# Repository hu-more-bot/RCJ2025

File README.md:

# RCJ2025
F1 Car Software & Hardware
> Huge thanks to [the6p4c](https://github.com/the6p4c/rp2040_ov2640) for his camera implementation

> More documentation is coming soon!

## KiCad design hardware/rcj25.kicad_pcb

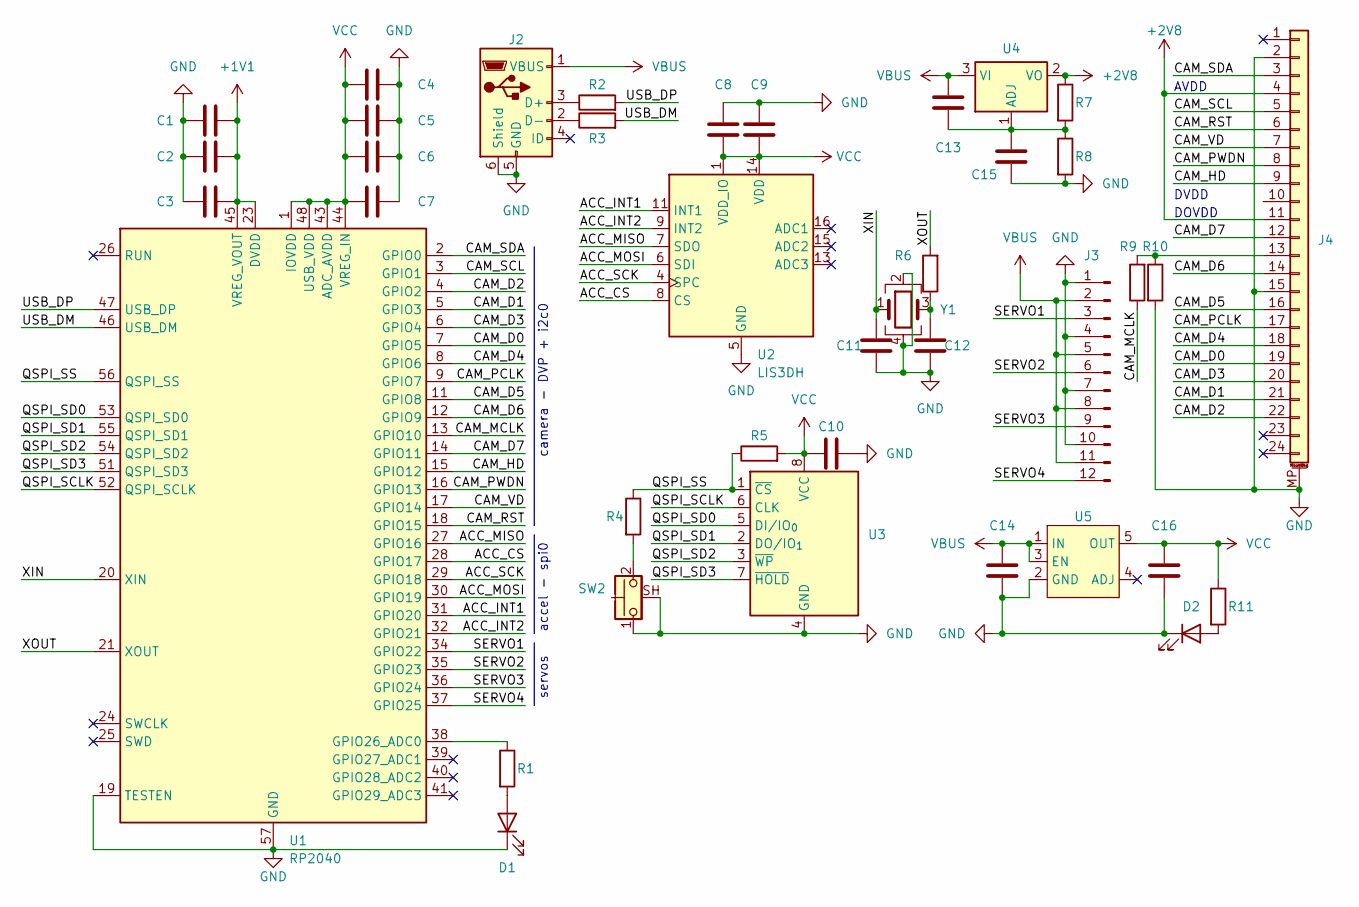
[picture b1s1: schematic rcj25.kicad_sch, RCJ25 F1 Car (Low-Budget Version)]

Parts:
C1, C2, C4, C5, C6, C8, C10: 100n; C_0603_1608Metric
C3, C7, C14, C16: 1u; C_0603_1608Metric
C9: 10u; C_0603_1608Metric
C11, C12, C13, C15: C; C_0603_1608Metric
D1: LED; LED_0603_1608Metric
D2: pwr; LED_0603_1608Metric
J2: USB_B_Micro; SHOUHAN_MicroQTJ
J3: Conn_01x12_Pin; PinHeader_3x04_P2.54mm_Vertical
J4: Conn_01x24_MountingPin; PCA-6G-24-HL-3
R1, R7, R8, R11: R; R_0603_1608Metric
R2, R3: 27.4; R_0603_1608Metric
R4, R6: 1k; R_0603_1608Metric
R5: DNF; R_0603_1608Metric
R9, R10: 4.7k; R_0603_1608Metric
SW2: SW_Push_Shielded; KSM632B
U1: RP2040; QFN-56-1EP_7x7mm_P0.4mm_EP3.2x3.2mm
U2: LIS3DH; LGA-16_3x3mm_P0.5mm_LayoutBorder3x5y
U3: W25X40CLSV; SOIC-8_5.3x5.3mm_P1.27mm
U4: LM1117MP-ADJ; SOT-223-3_TabPin2
U5: AP7365; SOT-23-5
Y1: Crystal_GND24; Crystal_SMD_3225-4Pin_3.2x2.5mm

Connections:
+1V1: C1.2, C2.2, C3.2, U1.23 (DVDD), U1.45 (VREG_VOUT), U1.50 (DVDD)
+2V8: J4.4, J4.11, R7.1, U4.2 (VO)
/ACC_CS: U1.28 (GPIO17), U2.8 (CS)
/ACC_INT1: U1.31 (GPIO20), U2.11 (INT1)
/ACC_INT2: U1.32 (GPIO21), U2.9 (INT2)
/ACC_MISO: U1.27 (GPIO16), U2.7 (SDO)
/ACC_MOSI: U1.30 (GPIO19), U2.6 (SDI)
/ACC_SCK: U1.29 (GPIO18), U2.4 (SPC)
/CAM_D0: J4.19, U1.7 (GPIO5)
/CAM_D1: J4.21, U1.5 (GPIO3)
/CAM_D2: J4.22, U1.4 (GPIO2)
/CAM_D3: J4.20, U1.6 (GPIO4)
/CAM_D4: J4.18, U1.8 (GPIO6)
/CAM_D5: J4.16, U1.11 (GPIO8)
/CAM_D6: J4.14, U1.12 (GPIO9)
/CAM_D7: J4.12, U1.14 (GPIO11)
/CAM_HD: J4.9, U1.15 (GPIO12)
/CAM_MCLK: R9.1, U1.13 (GPIO10)
/CAM_PCLK: J4.17, U1.9 (GPIO7)
/CAM_PWDN: J4.8, U1.16 (GPIO13)
/CAM_RST: J4.6, U1.18 (GPIO15)
/CAM_SCL: J4.5, U1.3 (GPIO1)
/CAM_SDA: J4.3, U1.2 (GPIO0)
/CAM_VD: J4.7, U1.17 (GPIO14)
/QSPI_SCLK: U1.52 (QSPI_SCLK), U3.6 (CLK)
/QSPI_SD0: U1.53 (QSPI_SD0), U3.5 (DI/IO_{0})
/QSPI_SD1: U1.55 (QSPI_SD1), U3.2 (DO/IO_{1})
/QSPI_SD2: U1.54 (QSPI_SD2), U3.3 (~WP)
/QSPI_SD3: U1.51 (QSPI_SD3), U3.7 (~HOLD)
/QSPI_SS: R4.1, R5.1, U1.56 (QSPI_SS), U3.1 (~CS)
/SERVO1: J3.3, U1.34 (GPIO22)
/SERVO2: J3.6, U1.35 (GPIO23)
/SERVO3: J3.9, U1.36 (GPIO24)
/SERVO4: J3.12, U1.37 (GPIO25)
/USB_DM: R3.2, U1.46 (USB_DM)
/USB_DP: R2.2, U1.47 (USB_DP)
/XIN: C11.2, U1.20 (XIN), Y1.1
/XOUT: R6.2, U1.21 (XOUT)
GND: C1.1, C2.1, C3.1, C4.2, C5.2, C6.2, C7.2, C8.1, C9.1, C10.2, C11.1, C12.1, C14.2, C15.2, C16.2, D1.1 (K), D2.1 (K), J2.5 (GND), J2.6 (Shield), J3.1, J3.4, J3.7, J3.10, J4.2, J4.15, J4.MP (MountPin), R8.2, R10.2, SW2.1, SW2.SH (B), U1.19 (TESTEN), U1.57 (GND), U2.5 (GND), U2.10 (GND), U2.12 (GND), U3.4 (GND), U5.2 (GND), Y1.2, Y1.4
unnamed: C12.2, R6.1, Y1.3
unnamed: D1.2 (A), R1.2
unnamed: D2.2 (A), R11.2
unnamed: J2.3 (D+), R2.1
unnamed: J2.2 (D-), R3.1
unnamed: J4.13, R9.2, R10.1
unnamed: R4.2, SW2.2
unnamed: R1.1, U1.38 (GPIO26_ADC0)
unnamed: C13.2, C15.1, R7.2, R8.1, U4.1 (ADJ)
VBUS: C13.1, C14.1, J2.1 (VBUS), J3.2, J3.5, J3.8, J3.11, U4.3 (VI), U5.1 (IN), U5.3 (EN)
VCC: C4.1, C5.1, C6.1, C7.1, C8.2, C9.2, C10.1, C16.1, R5.2, R11.1, U1.1 (IOVDD), U1.10 (IOVDD), U1.22 (IOVDD), U1.33 (IOVDD), U1.42 (IOVDD), U1.43 (ADC_AVDD), U1.44 (VREG_IN), U1.48 (USB_VDD), U1.49 (IOVDD), U2.1 (VDD_IO), U2.14 (VDD), U3.8 (VCC), U5.5 (OUT)

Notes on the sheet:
AVDD
DOVDD
servos
DVDD
accel - spi0
camera - DVP + i2c0

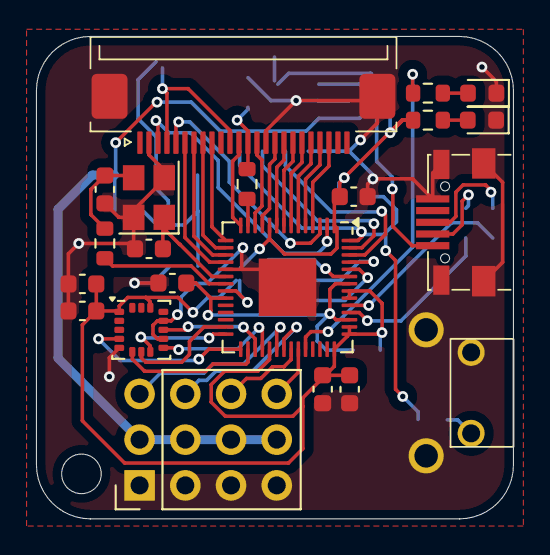
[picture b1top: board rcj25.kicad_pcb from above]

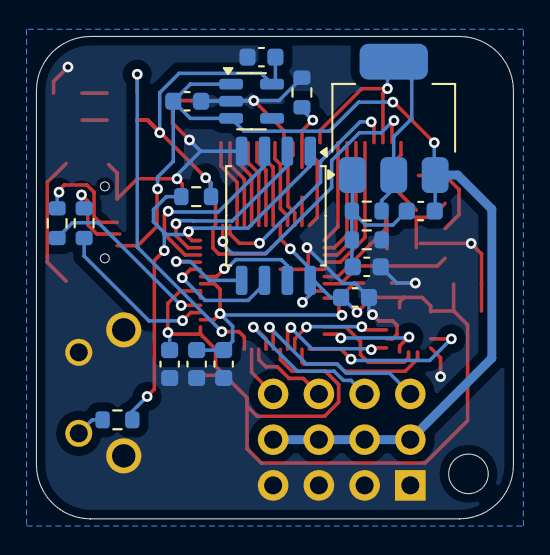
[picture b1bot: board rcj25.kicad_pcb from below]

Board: 2 copper layers, 26.5 x 26.8 mm, 39 parts (18 on the bottom side), 50 nets.

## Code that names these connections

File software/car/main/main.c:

// // #include <boards/pico.h>
#include <hardware/gpio.h>
// #include <hardware/spi.h>
// #include <hardware/i2c.h>
#include <pico/time.h>

#include <motor.h>
// #include <pico/stdio.h>

#define SERVO1 22
#define SERVO2 23
#define SERVO3 24
#define SERVO4 25

int main() {
  // Servo
  motor_init(SERVO2);
  motor_set(SERVO2, 1500);
  
  // BLDC
  sleep_ms(2000);
  motor_init(SERVO1);
  motor_set(SERVO1, 2000);
  sleep_ms(2000);
  motor_set(SERVO1, 1000);
  sleep_ms(2000);
  motor_set(SERVO1, 500);
  sleep_ms(2000);

  // motor_set(SERVO2, 1000);
  // motor_set(SERVO1, 1200);
  // sleep_ms(500);

  // for (int i = 0; i < 16 * 2; i++) {
  //   motor_set(SERVO1, 1100);
  //   sleep_ms(1500);
  //   // motor_set(SERVO1, 1000);
  //   // sleep_ms(300);
  // }

  motor_set(SERVO1, 1200);
  sleep_ms(250);
  motor_set(SERVO1, 1300);
  motor_set(SERVO2, 1000);
  sleep_ms(15000);

  motor_set(SERVO1, 1000);
  
  // motor_set(SERVO2, 1800);
  // sleep_ms(500);

  // motor_set(SERVO1, 1000);
  // motor_set(SERVO2, 1500);

  while(1) {
      // motor_set(SERVO2, 1200);
      // sleep_ms(1000);
      // motor_set(SERVO2, 1500);
      // sleep_ms(1000);
      // motor_set(SERVO2, 1800);
      // sleep_ms(1000);
      // motor_set(SERVO2, 1500);
      // sleep_ms(1000);
    }
}

// int main() {
//   // Camera
//   gpio_init(0); // SDA
//   gpio_set_function(0, GPIO_FUNC_I2C);
//   gpio_pull_up(0);

//   gpio_init(1); // SCL
//   gpio_set_function(1, GPIO_FUNC_I2C);
//   gpio_pull_up(1);

//   i2c_init(i2c0, 100000); // 100kHz

//   gpio_init(5); // io
//   gpio_init(3);
//   gpio_init(2);
//   gpio_init(4);
//   gpio_init(6);
//   gpio_init(8);
//   gpio_init(9);
//   gpio_init(11);

//   gpio_init(7); // pclk
//   gpio_init(10); // mclk
//   gpio_init(12); // hd
//   gpio_init(13); // pwdn
//   gpio_init(14); // vd
//   gpio_init(15); // rst

//   // Accelerometer
//   spi_init(spi0, 1000 * 1000);
//   gpio_set_function(16, GPIO_FUNC_SPI);
//   gpio_init(17);
//   gpio_set_function(18, GPIO_FUNC_SPI);
//   gpio_set_function(19, GPIO_FUNC_SPI);

//   gpio_init(20);
//   gpio_init(21);

//   // BLDC
//   bldc_init(22);

//   bldc_set_speed(22, 2000);
//   sleep_ms(1000);
//   bldc_set_speed(22, 1000);
//   sleep_ms(2000);

//   while (1) {
//     bldc_set_speed(22, 1100);
//   }

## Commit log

2025-03-19 hardware v0.1 & dev software
2025-03-20 fix test files
2025-03-28 .gitignore
2025-03-28 second times the charm
2025-03-28 fix segfault on some machines
2025-03-28 fix line detection
2025-03-28 early road direction detection
2025-03-30 early car software
2025-04-01 kill me
2025-04-02 rasp
2025-04-02 stuff ig
2025-04-02 stuffer
2025-04-03 lots
2025-04-03 why no work?
2025-04-04 arduino
2025-04-04 she go brrr
2025-06-06 I see light
2025-06-06 almost works
